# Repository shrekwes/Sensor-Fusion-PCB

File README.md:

# PyFusion — RP2040 Sensor Fusion Board

A compact, custom-fabricated two-layer sensor fusion PCB built around the Raspberry Pi RP2040. Integrates a 6-axis IMU, 3-axis magnetometer, and barometric pressure sensor on a single board — programmable natively in MicroPython.

---

## Hardware

| Component | Part | Interface | Address |
|---|---|---|---|
| Microcontroller | RP2040 (dual-core Cortex-M0+, 133MHz) | — | — |
| IMU | IAM-20680HV (6-axis accel + gyro) | I2C1 — GP2/GP3 | 0x68 |
| Magnetometer | IIS2MDCTR (3-axis AMR) | I2C0 — GP8/GP9 | 0x1E |
| Barometer | BMP581 (pressure + temperature) | SoftI2C — GP6/GP7 | 0x46 |
| Flash | W25Q128JVS (128Mbit QuadSPI) | QSPI | — |
| Crystal | ABM8-272-T3 (12MHz) | XIN/XOUT | — |
| Regulator | NCP1117-3.3 (5V → 3.3V LDO) | — | — |

---

## PCB Design

The board is a two-layer design captured in KiCad 9.0. Layout decisions were driven primarily by the sensitivity requirements of the three MEMS sensors.

### Layer Stack

- **Top layer** — signal routing and 3.3V power polygon pour
- **Bottom layer** — continuous ground plane for low-impedance return paths and shielding, with minimal routing tracks

### Sensor Placement

**IMU (IAM-20680HV)**
Placed on a mechanically stable region of the board, away from mounting holes and connectors. Requires a solid ground plane beneath it for noise reduction — copper fill is maintained under this device. The exposed ground pad is connected to the ground plane via multiple vias.

**Magnetometer (IIS2MDCTR)**
Highly sensitive to magnetic fields from nearby copper currents. Ground plane and copper pours are cleared on both layers in the region surrounding this device. High-current traces and switching components are kept at a distance.

**Barometer (BMP581)**
Isolated from large copper regions on both layers to prevent thermal gradients and mechanical stress from influencing pressure readings.

### Key Layout Decisions

**Decoupling** — All bypass capacitors placed within 1–2mm of their associated VDD pins, with short via stubs to the ground plane, in accordance with each sensor's datasheet.

**Crystal** — ABM8-272-T3 placed as close as practical to the RP2040 XIN/XOUT pins. Load capacitors are inline. A copper pour guard ring tied to GND prevents switching-noise coupling into the oscillator.

**USB differential pair** — USBDP/USBDM routed as a 90Ω differential pair (0.8mm track width, 0.15mm gap on a 1mm substrate) per the RP2040 hardware design guide.

**GPIO header** — 23 pins expose selected RP2040 GPIO signals for external interfacing via UART, SPI, or I2C, making the board extensible rather than a closed system.

**BOOTSEL and RESET** — dedicated push-buttons for bootloader entry and manual reset.

### KiCad Footprint Note

The IAM-20680HV KiCad footprint files were not available at the time of design. The **ICM-20602** footprint was used as a drop-in substitute — the two devices share an identical package and pin layout. The assembled board uses the IAM-20680HV component on the ICM-20602 footprint without modification.

### Design Verification

Before manufacture the following checks were completed in KiCad:
- Electrical Rules Check (ERC) — no unconnected pins or conflicting power nets
- Design Rules Check (DRC) — cleared against manufacturer minimums (trace width, clearance, via drill, annular ring)
- Footprint verification — each land pattern cross-checked against the manufacturer datasheet
- Gerber preview — layer stack-up, drill file, and copper patterns confirmed

---

## Firmware

All firmware is written in MicroPython and runs directly on the RP2040. The board was developed and flashed using Thonny IDE.

### File Overview

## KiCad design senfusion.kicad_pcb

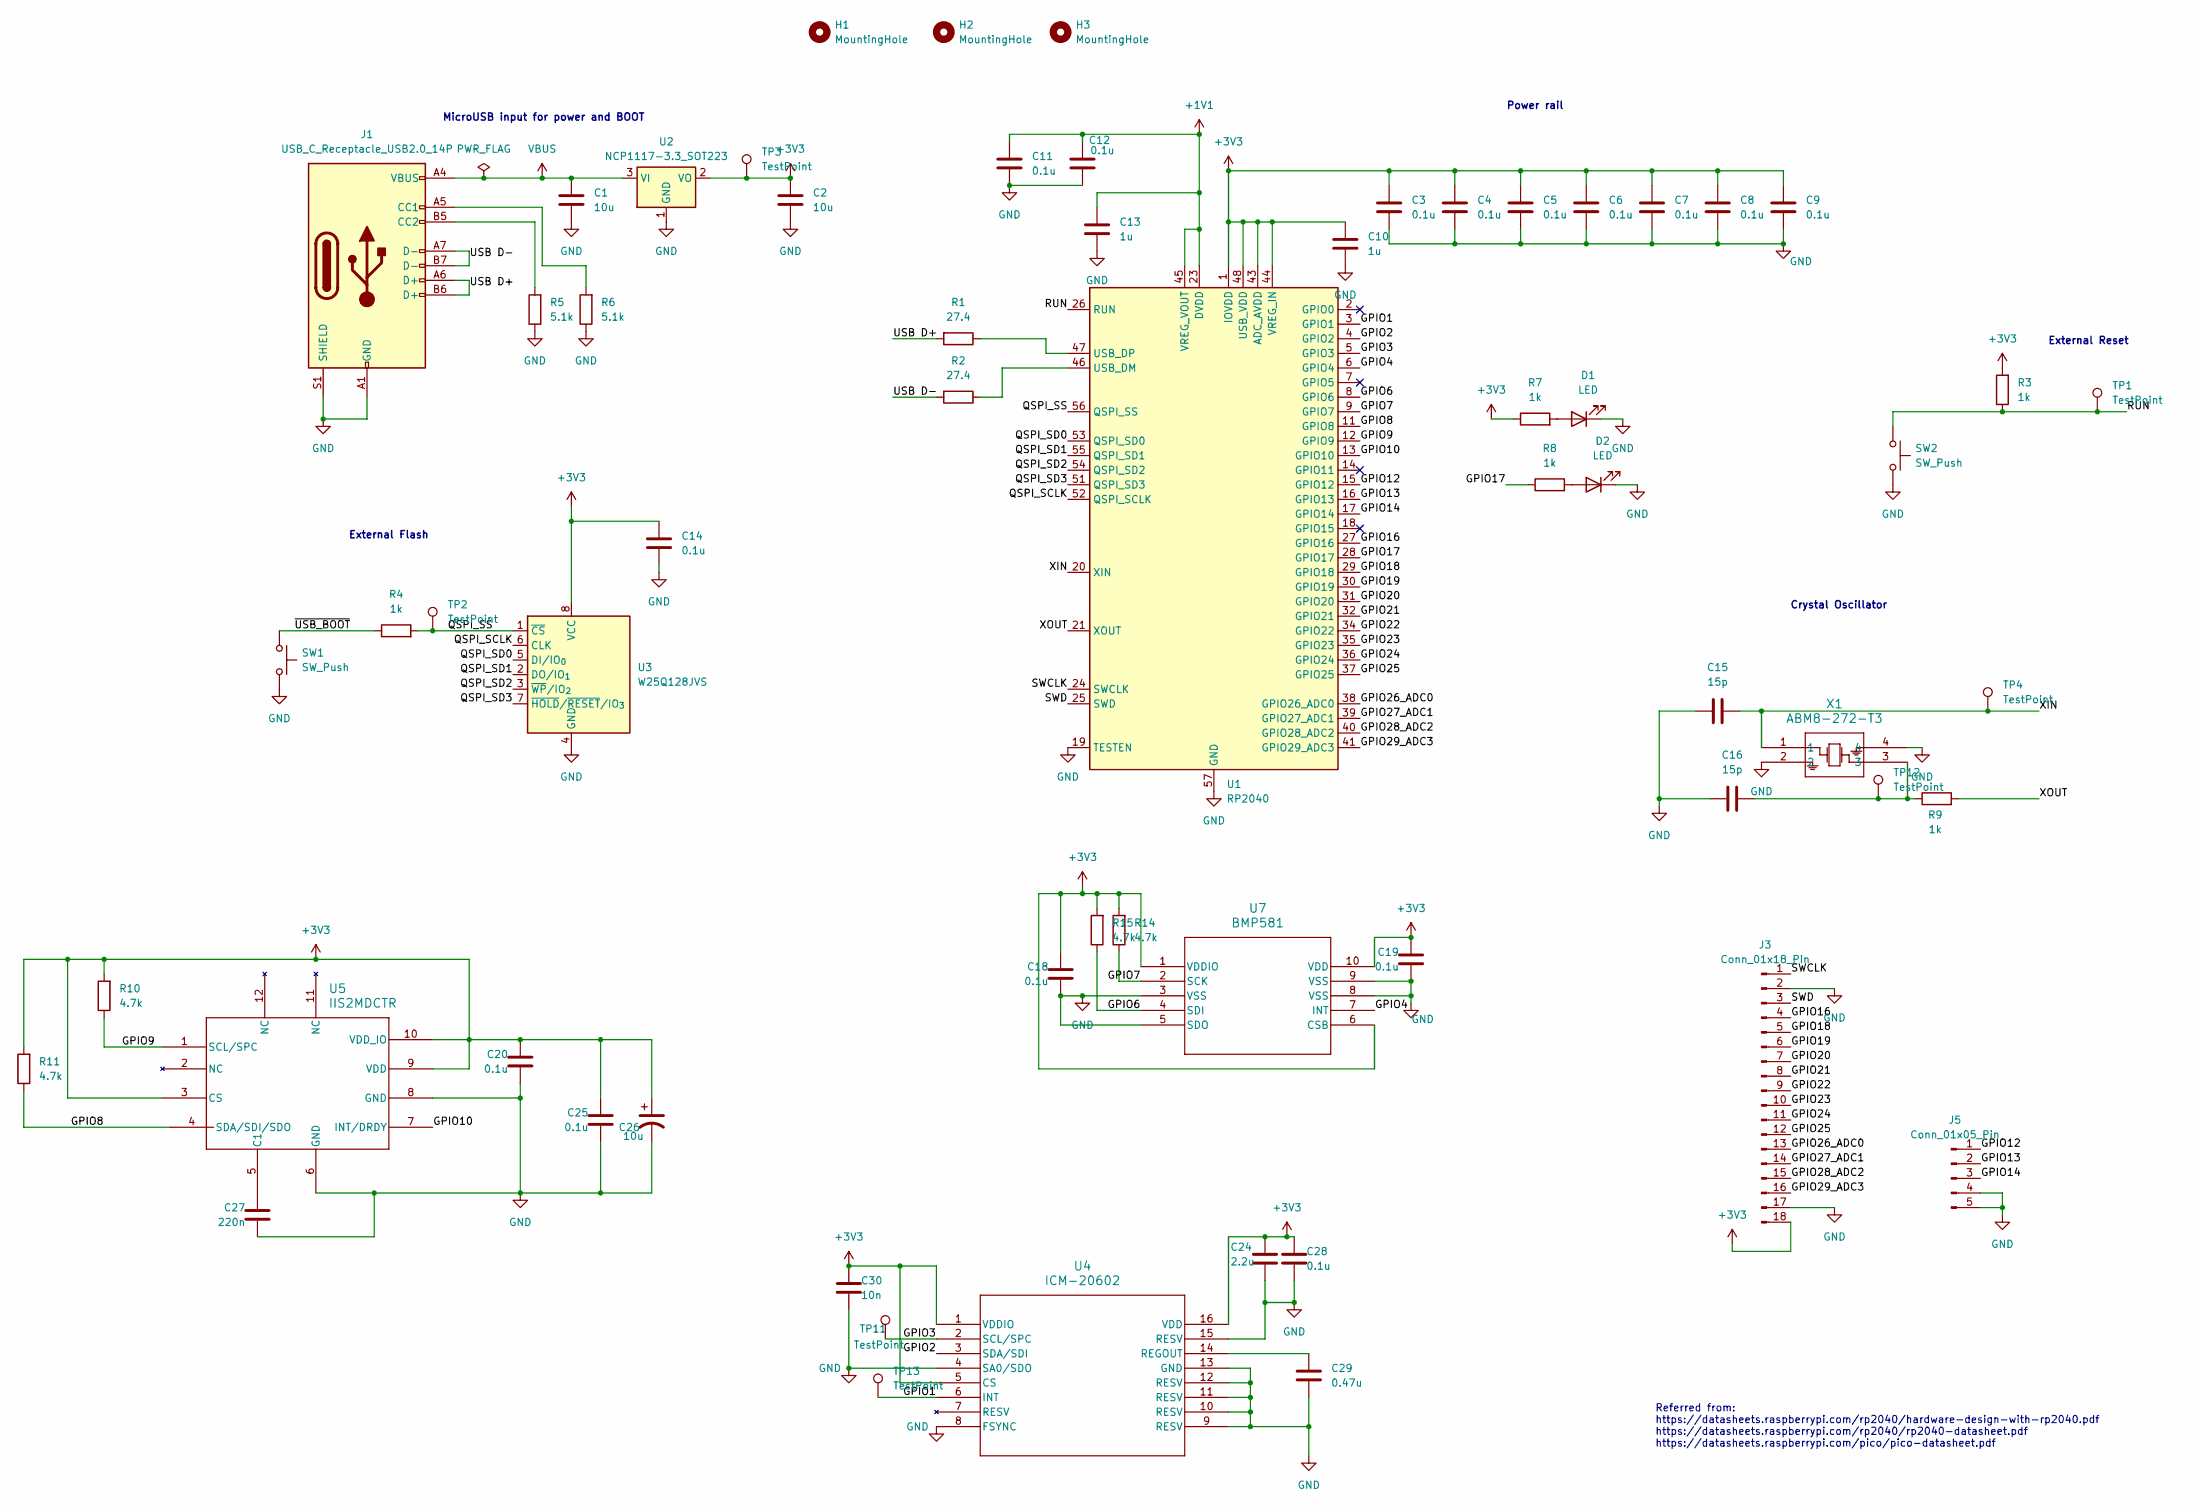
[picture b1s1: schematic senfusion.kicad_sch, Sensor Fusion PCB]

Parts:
C1, C2, C26: 10u; C_0603_1608Metric
C3, C4, C5, C6, C7, C8, C9, C11, C12, C14, C18, C19, C20, C25, C28: 0.1u; C_0402_1005Metric
C10, C13: 1u; C_0402_1005Metric
C15, C16: 15p; C_0402_1005Metric
C24: 2.2u; C_0402_1005Metric
C27: 220n; C_0402_1005Metric
C29: 0.47u; C_0402_1005Metric
C30: 10n; C_0402_1005Metric
D1, D2: LED; LED_0402_1005Metric
H1, H2, H3: MountingHole; MountingHole_2.2mm_M2
J1: USB_C_Receptacle_USB2.0_14P; USB_C_Receptacle_GCT_USB4105-xx-A_16P_TopMnt_Horizontal
J3: Conn_01x18_Pin; PinHeader_1x18_P2.54mm_Vertical
J5: Conn_01x05_Pin; PinHeader_1x05_P2.54mm_Vertical
R1, R2: 27.4; R_0402_1005Metric
R3, R4, R7, R8, R9: 1k; R_0402_1005Metric
R5, R6: 5.1k; R_0402_1005Metric
R10, R11, R14, R15: 4.7k; R_0402_1005Metric
SW1, SW2: SW_Push; SW_Push_1P1T_NO_CK_KMR2
TP1, TP2, TP3, TP4, TP11, TP12, TP13: TestPoint; TestPoint_Pad_D1.5mm
U1: RP2040; QFN-56-1EP_7x7mm_P0.4mm_EP3.2x3.2mm
U2: NCP1117-3.3_SOT223; SOT-223-3_TabPin2
U3: W25Q128JVS; SOIC-8_5.3x5.3mm_P1.27mm
U4: ICM-20602; LGA16_I62_IVS
U5: IIS2MDCTR; LGA-12_2X2X0P7_STM
U7: BMP581; QFN10_BMP581_BOS
X1: ABM8-272-T3; ABM8-272-T3_ABR

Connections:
+1V1: C11.1, C12.1, C13.1, U1.23 (DVDD), U1.45 (VREG_VOUT), U1.50 (DVDD)
+3V3: C2.1, C3.1, C4.1, C5.1, C6.1, C7.1, C8.1, C9.1, C10.1, C14.1, C18.1, C19.1, C20.1, C24.1, C25.1, C26.1, C28.1, C30.1, J3.18, R3.2, R7.1, R10.2, R11.2, R14.2, R15.2, TP3.1, U1.1 (IOVDD), U1.10 (IOVDD), U1.22 (IOVDD), U1.33 (IOVDD), U1.42 (IOVDD), U1.43 (ADC_AVDD), U1.44 (VREG_IN), U1.48 (USB_VDD), U1.49 (IOVDD), U2.2 (VO), U3.8 (VCC), U4.1 (VDDIO), U4.5 (CS), U4.16 (VDD), U5.3 (CS), U5.9 (VDD), U5.10 (VDD_IO), U7.1 (VDDIO), U7.6 (CSB), U7.10 (VDD)
/GPIO1: TP13.1, U1.3 (GPIO1), U4.6 (INT)
/GPIO2: U1.4 (GPIO2), U4.3 (SDA/SDI)
/GPIO3: TP11.1, U1.5 (GPIO3), U4.2 (SCL/SPC)
/GPIO4: U1.6 (GPIO4), U7.7 (INT)
/GPIO6: R15.1, U1.8 (GPIO6), U7.4 (SDI)
/GPIO7: R14.1, U1.9 (GPIO7), U7.2 (SCK)
/GPIO8: R11.1, U1.11 (GPIO8), U5.4 (SDA/SDI/SDO)
/GPIO9: R10.1, U1.12 (GPIO9), U5.1 (SCL/SPC)
/GPIO10: U1.13 (GPIO10), U5.7 (INT/DRDY)
/GPIO12: J5.1, U1.15 (GPIO12)
/GPIO13: J5.2, U1.16 (GPIO13)
/GPIO14: J5.3, U1.17 (GPIO14)
/GPIO16: J3.4, U1.27 (GPIO16)
/GPIO17: R8.1, U1.28 (GPIO17)
/GPIO18: J3.5, U1.29 (GPIO18)
/GPIO19: J3.6, U1.30 (GPIO19)
/GPIO20: J3.7, U1.31 (GPIO20)
/GPIO21: J3.8, U1.32 (GPIO21)
/GPIO22: J3.9, U1.34 (GPIO22)
/GPIO23: J3.10, U1.35 (GPIO23)
/GPIO24: J3.11, U1.36 (GPIO24)
/GPIO25: J3.12, U1.37 (GPIO25)
/GPIO26_ADC0: J3.13, U1.38 (GPIO26_ADC0)
/GPIO27_ADC1: J3.14, U1.39 (GPIO27_ADC1)
/GPIO28_ADC2: J3.15, U1.40 (GPIO28_ADC2)
/GPIO29_ADC3: J3.16, U1.41 (GPIO29_ADC3)
/QSPI_SCLK: U1.52 (QSPI_SCLK), U3.6 (CLK)
/QSPI_SD0: U1.53 (QSPI_SD0), U3.5 (DI/IO_{0})
/QSPI_SD1: U1.55 (QSPI_SD1), U3.2 (DO/IO_{1})
/QSPI_SD2: U1.54 (QSPI_SD2), U3.3 (~WP/IO_{2})
/QSPI_SD3: U1.51 (QSPI_SD3), U3.7 (~HOLD/~RESET/IO_{3})
/QSPI_SS: R4.2, TP2.1, U1.56 (QSPI_SS), U3.1 (~CS)
/RUN: R3.1, SW2.1, TP1.1, U1.26 (RUN); also elsewhere on the board
/SWCLK: J3.1, U1.24 (SWCLK)
/SWD: J3.3, U1.25 (SWD)
/USB D+: J1.A6 (D+), J1.B6 (D+), R1.2
/USB D-: J1.A7 (D-), J1.B7 (D-), R2.2
/XIN: C15.1, TP4.1, U1.20 (XIN), X1.1
/XOUT: R9.2, U1.21 (XOUT)
/~USB_BOOT: R4.1, SW1.1; also elsewhere on the board
GND: C1.2, C2.2, C3.2, C4.2, C5.2, C6.2, C7.2, C8.2, C9.2, C10.2, C11.2, C12.2, C13.2, C14.2, C15.2, C16.2, C18.2, C19.2, C20.2, C24.2, C25.2, C26.2, C27.2, C28.2, C29.2, C30.2, D1.1 (K), D2.1 (K), J1.A1 (GND), J1.A12 (GND), J1.B1 (GND), J1.B12 (GND), J1.S1 (SHIELD), J3.2, J3.17, J5.4, J5.5, R5.1, R6.1, SW1.2, SW2.2, U1.19 (TESTEN), U1.57 (GND), U2.1 (GND), U3.4 (GND), U4.4 (SA0/SDO), U4.8 (FSYNC), U4.9 (RESV), U4.10 (RESV), U4.11 (RESV), U4.12 (RESV), U4.13 (GND), U4.15 (RESV), U5.6 (GND), U5.8 (GND), U7.3 (VSS), U7.5 (SDO), U7.8 (VSS), U7.9 (VSS), X1.2, X1.4; also elsewhere on the board
unnamed: C16.1, R9.1, TP12.1, X1.3
unnamed: D1.2 (A), R7.2
unnamed: D2.2 (A), R8.2
unnamed: J1.A5 (CC1), R6.2
unnamed: J1.B5 (CC2), R5.2
unnamed: R2.1, U1.46 (USB_DM)
unnamed: R1.1, U1.47 (USB_DP)
unnamed: C29.1, U4.14 (REGOUT)
unnamed: C27.1, U5.5 (C1)
VBUS: C1.1, J1.A4 (VBUS), J1.A9 (VBUS), J1.B4 (VBUS), J1.B9 (VBUS), U2.3 (VI)

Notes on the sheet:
Referred from: https://datasheets.raspberrypi.com/rp2040/hardware-design-with-rp2040.pdf https://datasheets.raspberrypi.com/rp2040/rp2040-datasheet.pdf https://datasheets.raspberrypi.com/pico/pico-datasheet.pdf
Power rail
External Reset
External Flash
MicroUSB input for power and BOOT
Crystal Oscillator

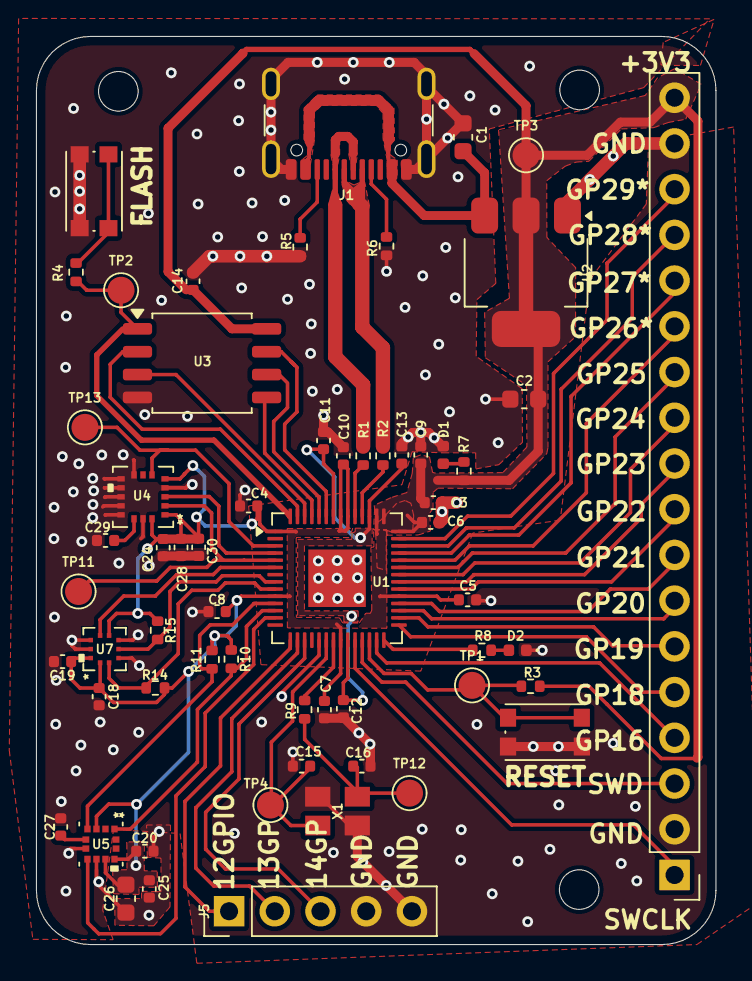
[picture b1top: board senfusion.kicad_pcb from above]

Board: 2 copper layers, 37.7 x 50.5 mm, 63 parts (0 on the bottom side), 53 nets.

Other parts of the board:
FLASH: SW_Push; SW_Push_1P1T_NO_CK_KMR2
RESET: SW_Push; SW_Push_1P1T_NO_CK_KMR2

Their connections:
/RUN: RESET.1; also elsewhere on the board
/~USB_BOOT: FLASH.1; also elsewhere on the board
GND: FLASH.2, RESET.2; also elsewhere on the board

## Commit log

2026-06-18 Rename New_design_new_sensors.kicad_pcb to senfusion.kicad_pcb
2026-06-18 Rename New_design_new_sensors.kicad_sch to senfusion.kicad_sch
2026-06-18 Rename New_design_new_sensors.kicad_pro to senfusion.kicad_pro
